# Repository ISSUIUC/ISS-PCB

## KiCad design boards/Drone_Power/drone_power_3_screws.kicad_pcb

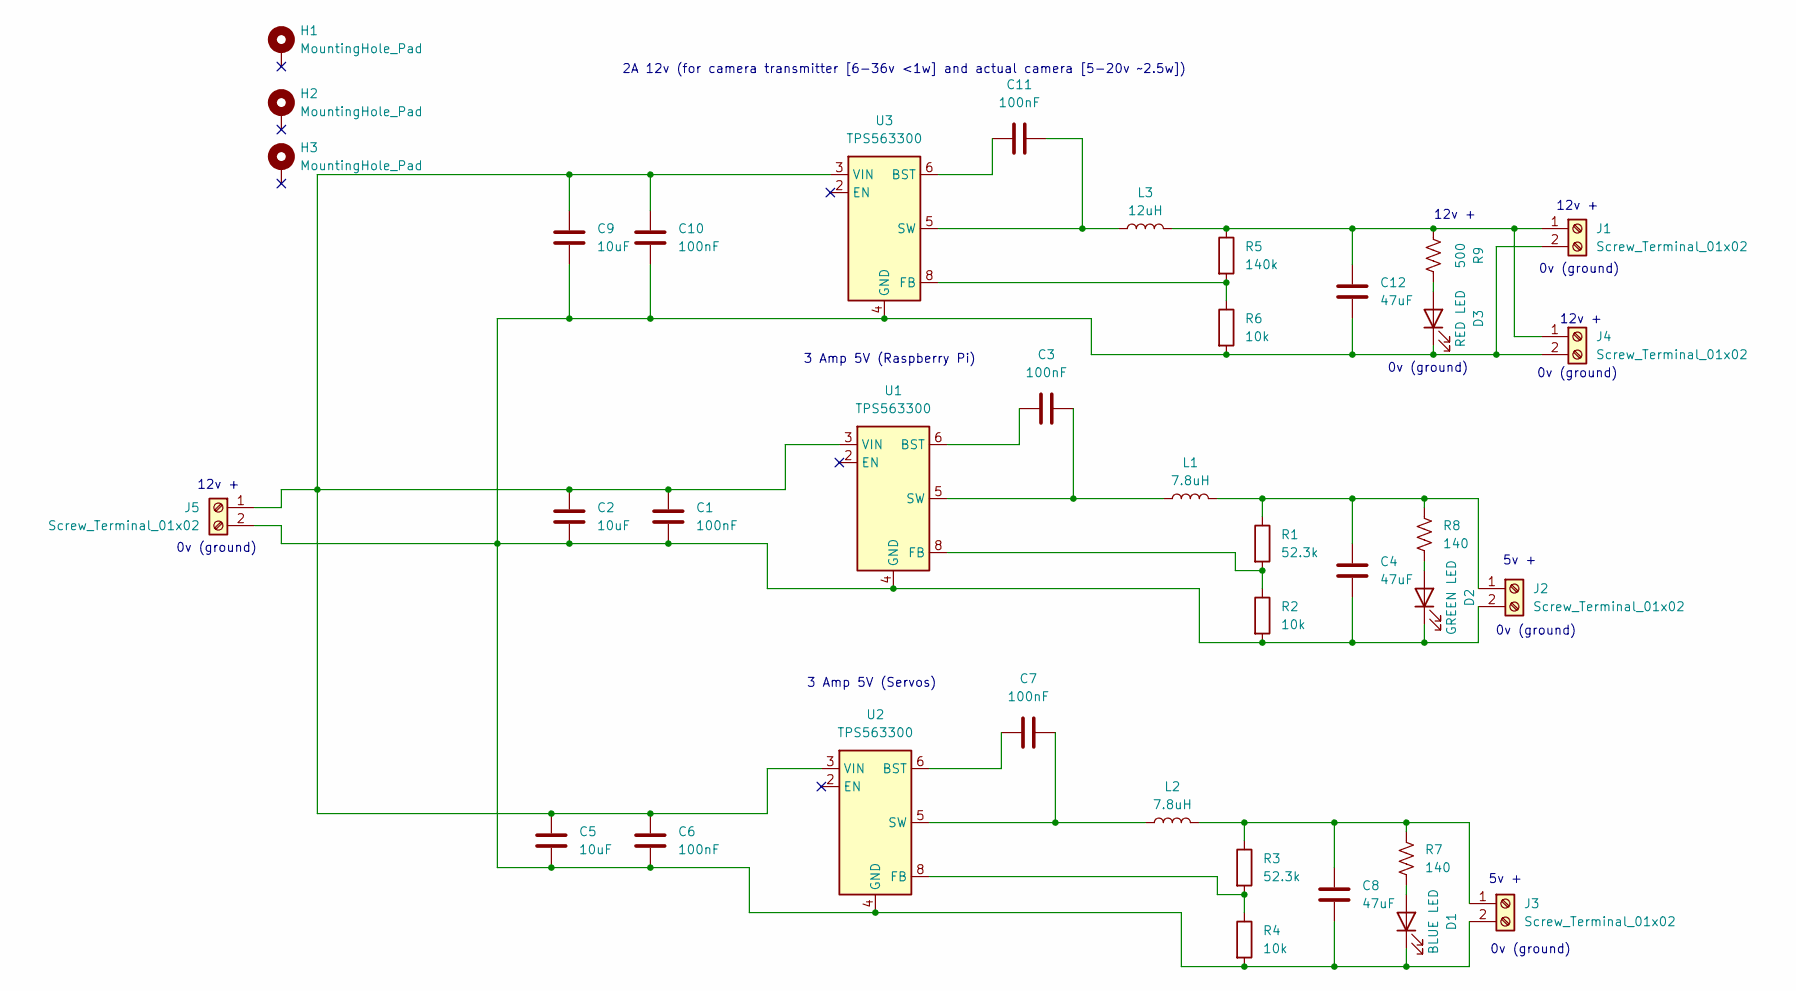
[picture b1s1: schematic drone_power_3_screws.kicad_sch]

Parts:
C1, C3, C6, C7, C10, C11: 100nF; C_0603_1608Metric
C2, C5, C9: 10uF; C_1206_3216Metric
C4, C8, C12: 47uF; C_1210_3225Metric
D1: BLUE LED; LED_0603_1608Metric
D2: GREEN LED; LED_0603_1608Metric
D3: RED LED; LED_0603_1608Metric
H1, H2, H3: MountingHole_Pad; MountingHole_3mm_Pad_Via
J1, J2, J3, J4, J5: Screw_Terminal_01x02; TE_282837-2
L1, L2: 7.8uH; L_Wuerth_HCI-1050
L3: 12uH; IND_XGL6060_COC
R1, R3: 52.3k; R_0603_1608Metric
R2, R4, R6: 10k; R_0603_1608Metric
R5: 140k; R_0603_1608Metric
R7, R8: 140; R_0603_1608Metric
R9: 500; R_0603_1608Metric
U1, U2, U3: TPS563300; SOT-583-8

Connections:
unnamed: D1.2 (A), R7.2
unnamed: C1.2, C2.2, C4.2, C5.2, C6.2, C8.2, C9.2, C10.2, C12.2, D1.1 (K), D2.1 (K), D3.1 (K), J1.2, J2.2, J3.2, J4.2, J5.2, R2.2, R4.2, R6.2, U1.4 (GND), U2.4 (GND), U3.4 (GND)
unnamed: D2.2 (A), R8.2
unnamed: D3.2 (A), R9.2
unnamed: C12.1, J1.1, J4.1, L3.2, R5.1, R9.1
unnamed: C4.1, J2.1, L1.2, R1.1, R8.1
unnamed: C8.1, J3.1, L2.2, R3.1, R7.1
unnamed: C1.1, C2.1, C5.1, C6.1, C9.1, C10.1, J5.1, U1.3 (VIN), U2.3 (VIN), U3.3 (VIN)
unnamed: C3.1, U1.6 (BST)
unnamed: R1.2, R2.1, U1.8 (FB)
unnamed: C3.2, L1.1, U1.5 (SW)
unnamed: C7.1, U2.6 (BST)
unnamed: R3.2, R4.1, U2.8 (FB)
unnamed: C7.2, L2.1, U2.5 (SW)
unnamed: C11.1, U3.6 (BST)
unnamed: R5.2, R6.1, U3.8 (FB)
unnamed: C11.2, L3.1, U3.5 (SW)

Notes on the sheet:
0v (ground)
12v +
3 Amp 5V (Raspberry Pi)
5v +
3 Amp 5V (Servos)
2A 12v (for camera transmitter [6-36v <1w] and actual camera [5-20v ~2.5w])

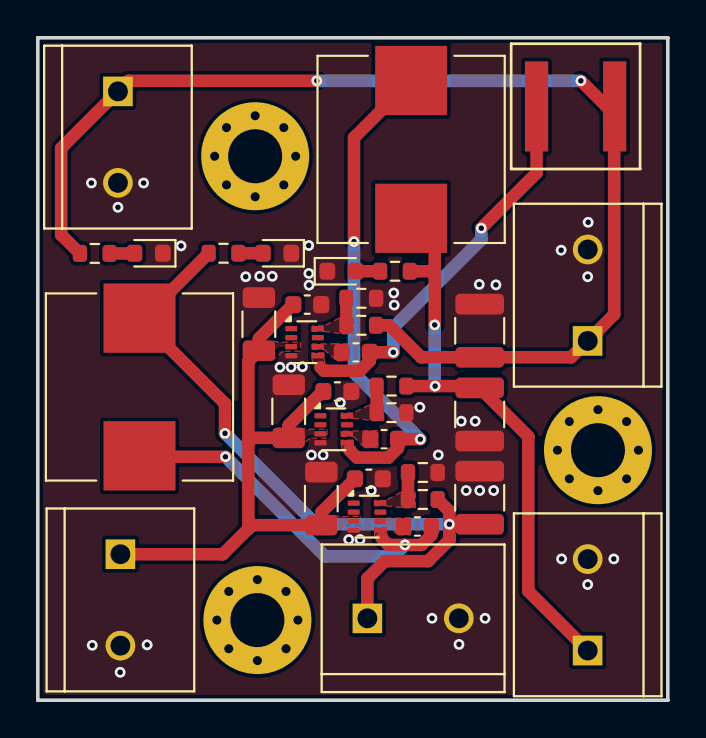
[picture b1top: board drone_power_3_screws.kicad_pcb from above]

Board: 2 copper layers, 35.0 x 36.8 mm, 38 parts (0 on the bottom side), 17 nets.

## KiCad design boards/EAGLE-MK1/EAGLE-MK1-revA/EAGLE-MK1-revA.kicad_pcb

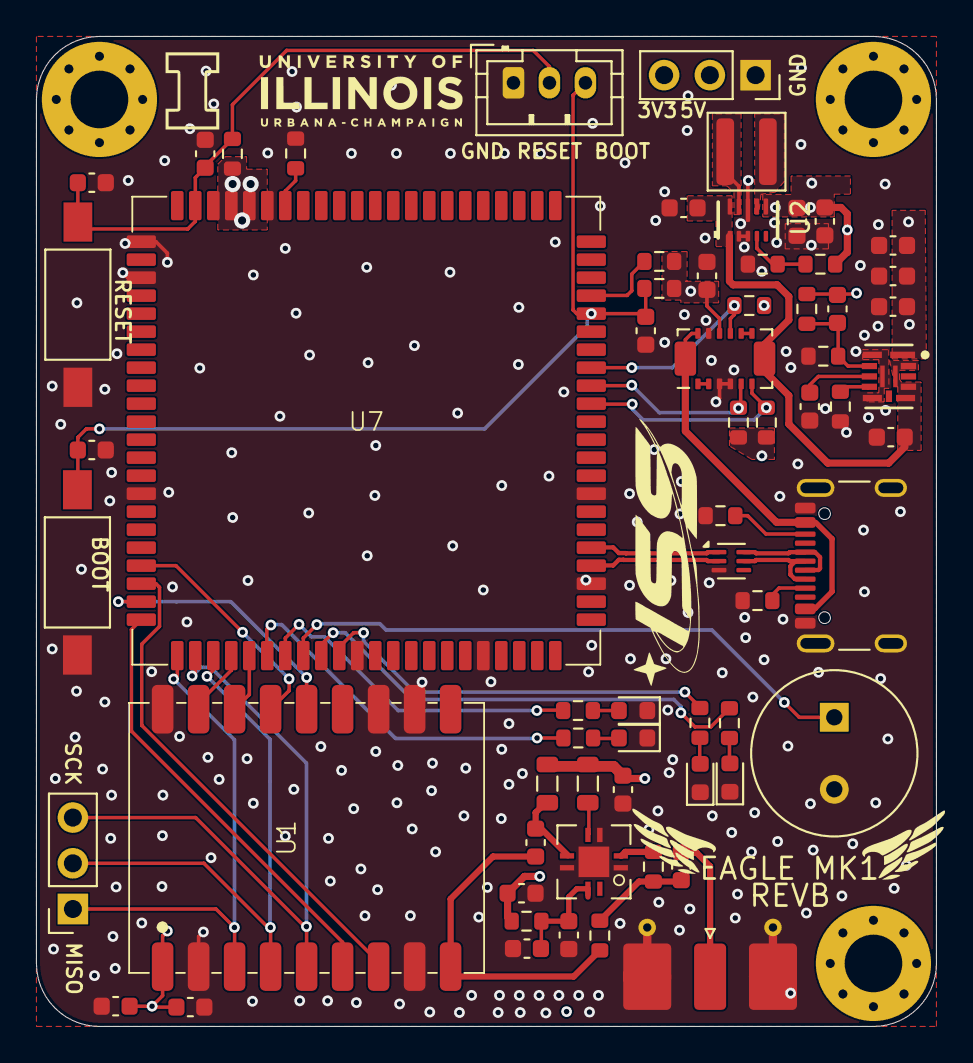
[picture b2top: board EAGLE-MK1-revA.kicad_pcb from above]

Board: 4 copper layers, 50.0 x 55.0 mm, 68 parts (0 on the bottom side), 51 nets.

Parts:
BZ101: Buzzer; MagneticBuzzer_PUI_AT-0927-TT-6-R
C1, C2, C4, C5, C6, C45, C48: 22uF; C_0603_1608Metric
C3, C7, C8, C31, C114: 100nF; C_0603_1608Metric
C10, C34, C36, C120: 1uF; C_0603_1608Metric
C33, C35, C37, C49: 100pF; C_0603_1608Metric
C46: 4.7nF; C_0603_1608Metric
C47: 10pF; C_0603_1608Metric
D104: RED LED; LED_0603_1608Metric
D105: ORANGE LED; LED_0603_1608Metric
D106: GREEN LED; LED_0603_1608Metric
D107: BLUE LED; LED_0603_1608Metric
H101, H103, H104: MountingHole; MountingHole_3.2mm_M3_Pad_Via
J1: SMA; SMA_Molex_73251-2120_EdgeMount_Horizontal
J101: USB4105-GF-A; USB_C_Receptacle_GCT_USB4105-xx-A_16P_TopMnt_Horizontal
J107: Conn_01x03; JST_PH_B3B-PH-K_1x03_P2.00mm_Vertical
J108, J109: Conn_01x03; PinSocket_1x03_P2.54mm_Vertical
L1: 36nH; L_0805_2012Metric
L2: 47nH; L_0805_2012Metric
L4: 470nH; L_Wuerth_MAPI-4030
R1: 806k; R_0603_1608Metric
R2: 91k; R_0603_1608Metric
R3, R4, R118, R119: 0; R_0603_1608Metric
R5, R14, R19, R116: 10k; R_0603_1608Metric
R16: 100k; R_0603_1608Metric
R18: 453k; R_0603_1608Metric
R105, R106: 5.1k; R_0603_1608Metric
R117, R122: 4.7k; R_0603_1608Metric
R140: 20k; R_0603_1608Metric
R141, R142, R143, R144: 470; R_0603_1608Metric
SW2, SW3: SW_Push; SW_SPST_FSMSM
U1: LR2021
U2: TPS63802; VSON-HR-DLA0010A
U4: PMA-545G1+; QFN-8-1EP_3x3mm_P1.2mm_EP1.7x1.7mm
U5: TPSM82813; QFN-FCMOD-VCA0013A
U7: ESP32-P4; ESP32-P4-Module
U101: ECMF02-2AMX6; ST_UQFN-6L_1.5x1.7mm_P0.5mm
U106: INA745x; VQFN-REL0014B

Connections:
+3V3: C4.2, C5.2, C10.1, C31.1, C47.2, C48.2, C114.1, J108.3, R5.2, R18.2, R19.2, R116.1, R117.1, R122.1, R140.2, U1.1 (VCC), U5.1 (VOUT), U7.84 (ESP_VBAT), U7.85 (ESP_3V3), U7.86 (ESP_3V3), U106.11 (VS)
+5V: C2.2, C6.2, C35.2, C36.2, J108.2, L1.2, L2.2, R1.1, R4.2, U2.6 (VOUT)
/Amplifer_Input: R118.1, U4.2 (RFIN)
/Antenna_Connector: C49.2, R118.2, R119.2
/BOOT_SW: C3.1, C8.1, J107.3, R5.1, SW3.1, U7.62 (GPIO35)
/BUZZER: BZ101.1 (-), U7.30 (GPIO21)
/D+: J101.A6 (D+), J101.B6 (D+), U101.6 (D+_out)
/D-: J101.A7 (D-), J101.B7 (D-), U101.5 (D-_out)
/LED_BLUE: R144.1, U7.29 (GPIO20)
/LED_GREEN: R143.1, U7.28 (GPIO13)
/LED_ORANGE: R142.1, U7.31 (GPIO22)
/LED_RED: R141.1, U7.32 (GPIO23)
/LR2021_ANT: C37.1, R119.1, U1.9 (ANT)
/LR2021_BUSY: U1.7 (BUSY), U7.20 (GPIO5)
/LR2021_CS: U1.6 (~CS), U7.22 (GPIO7)
/LR2021_DIO7: U1.17 (DIO7), U7.26 (GPIO11)
/LR2021_DIO8: U1.16 (DIO8), U7.27 (GPIO12)
/LR2021_DIO9: U1.15 (DIO9), U7.19 (GPIO4)
/LR2021_nRST: U1.14 (nRST), U7.21 (GPIO6)
/RESET_SW: C7.1, C120.1, J107.2, R140.1, SW2.1, U7.87 (CHIP_PU)
/SENSE_ALERT: R116.2, U7.59 (GPIO32), U106.10 (ALERT)
/SENSE_SCL: R122.2, U7.57 (GPIO30), U106.6 (SCL)
/SENSE_SDA: R117.2, U7.58 (GPIO31), U106.5 (SDA)
/SPI_MISO: J109.1, U1.3 (MISO), U7.23 (GPIO8)
/SPI_MOSI: J109.2, U1.4 (MOSI), U7.25 (GPIO10)
/SPI_SCK: J109.3, U1.5 (SCK), U7.24 (GPIO9)
/SYS_POWER: J101.A4 (VBUS), J101.A9 (VBUS), J101.B4 (VBUS), J101.B9 (VBUS), U106.13 (VBUS), U106.14 (IS+)
/USB_D+: U7.49 (DP), U101.1 (D+_in)
/USB_D-: U7.48 (DM), U101.2 (D-_in)
/VREG_IN: C1.2, C45.2, U2.1 (EN), U2.10 (VIN), U5.8 (VIN), U5.9 (EN), U5.11 (MODE_SYNC), U5.13 (VIN), U106.7 (IS-)
GND: BZ101.2 (+), C1.1, C2.1, C3.2, C4.1, C5.1, C6.1, C7.2, C8.2, C10.2, C31.2, C33.2, C34.2, C35.1, C36.1, C45.1, C46.1, C48.1, C114.2, C120.2, D104.1 (K), D105.1 (K), D106.1 (K), D107.1 (K), J1.2 (Ext), J101.A1 (GND), J101.A12 (GND), J101.B1 (GND), J101.B12 (GND), J101.S1 (SHIELD), J107.1, J108.1, R2.2, R3.2, R14.2, R16.1, R105.1, R106.1, SW2.2, SW3.2, U1.2 (GND), U1.8 (GND), U1.11 (GND), U1.12 (GND), U1.18 (GND), U2.2 (MODE), U2.3 (AGND), U2.8 (GND), U4.1 (NC), U4.3 (NC), U4.6 (NC), U4.9 (GND), U5.2 (GND), U5.6 (GND), U5.12 (GND), U7.1 (GND), U7.3 (GND), U7.15 (GND), U7.33 (GND), U7.40 (GND), U7.47 (GND), U7.52 (GND), U7.83 (GND), U101.3 (GND), U106.3 (A1), U106.4 (A0), U106.12 (GND)
unnamed: C33.1, C34.1, R4.1, U4.7 (BIAS)
unnamed: D104.2 (A), R141.2
unnamed: D105.2 (A), R142.2
unnamed: D106.2 (A), R143.2
unnamed: D107.2 (A), R144.2
unnamed: C49.1, J1.1 (In)
unnamed: J101.A5 (CC1), R105.2
unnamed: J101.B5 (CC2), R106.2
unnamed: L1.1, U4.4 (BIAS)
unnamed: R1.2, R2.1, U2.4 (FB)
unnamed: L4.1, U2.9 (L1)
unnamed: L4.2, U2.7 (L2)
unnamed: C37.2, L2.1, U4.5 (RFOUT)
unnamed: R14.1, U5.5 (COMP_FSET)
unnamed: C47.1, R16.2, R18.1, U5.3 (FB)
unnamed: C46.2, U5.4 (SS_TR)
unnamed: R19.1, U7.63 (GPIO36)
unnamed: R3.1, U7.82 (GPIO54)
unnamed: U106.1 (SH+), U106.2 (IN+)
unnamed: U106.8 (SH-), U106.9 (IN-)

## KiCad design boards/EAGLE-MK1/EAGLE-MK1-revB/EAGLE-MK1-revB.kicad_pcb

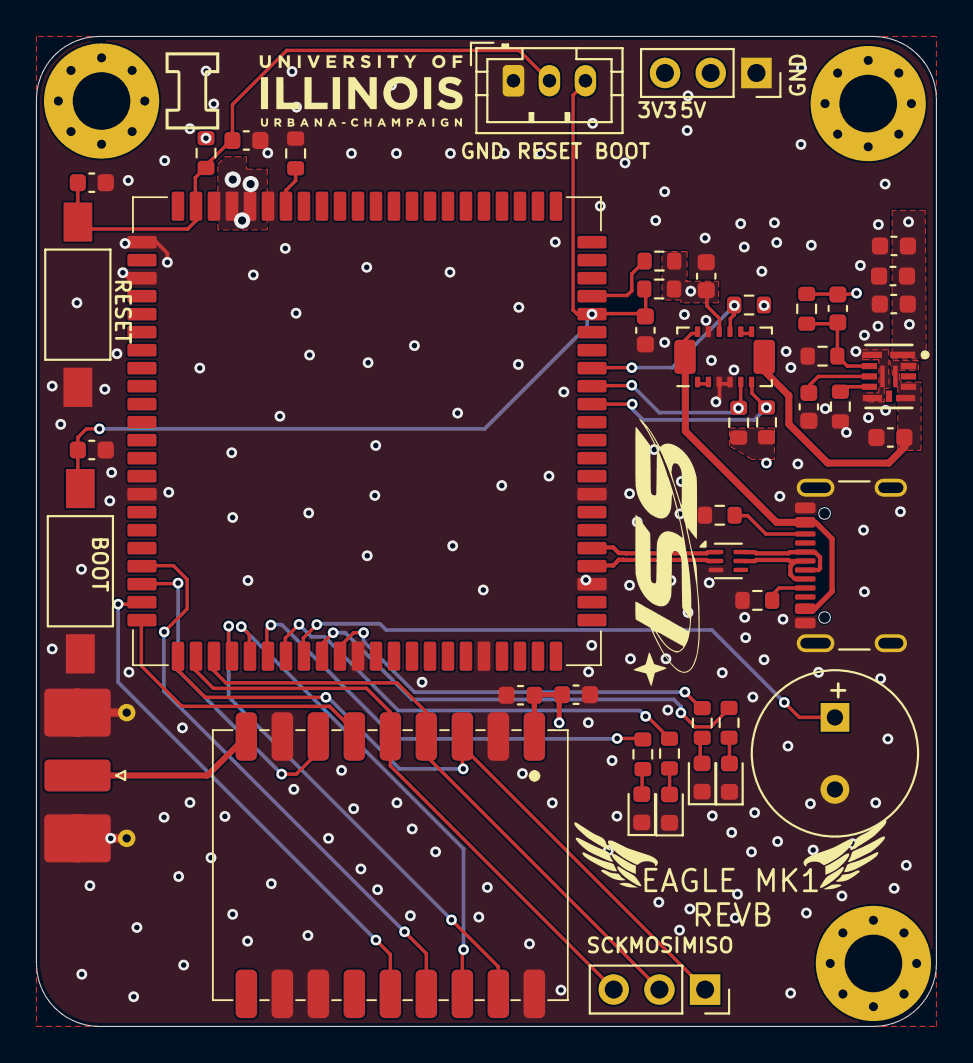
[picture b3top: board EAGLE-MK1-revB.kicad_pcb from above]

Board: 4 copper layers, 50.0 x 55.0 mm, 49 parts (0 on the bottom side), 41 nets.

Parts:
BZ1: Buzzer; MagneticBuzzer_PUI_AT-0927-TT-6-R
C1, C2, C3, C11, C13: 100nF; C_0603_1608Metric
C4, C8, C9, C10: 22uF; C_0603_1608Metric
C5, C12: 1uF; C_0603_1608Metric
C6: 4.7nF; C_0603_1608Metric
C7: 10pF; C_0603_1608Metric
D1: RED LED; LED_0603_1608Metric
D2: ORANGE LED; LED_0603_1608Metric
D3: GREEN LED; LED_0603_1608Metric
D4: BLUE LED; LED_0603_1608Metric
H1, H2, H3: MountingHole; MountingHole_3.2mm_M3_Pad_Via
J1: USB4105-GF-A; USB_C_Receptacle_GCT_USB4105-xx-A_16P_TopMnt_Horizontal
J2, J5: Conn_01x03; PinSocket_1x03_P2.54mm_Vertical
J3: Conn_01x03; JST_PH_B3B-PH-K_1x03_P2.00mm_Vertical
J4: SMA; SMA_Molex_73251-2120_EdgeMount_Horizontal
R1, R2: 5.1k; R_0603_1608Metric
R3: 0; R_0603_1608Metric
R4, R5: 4.7k; R_0603_1608Metric
R6, R7, R9, R16: 10k; R_0603_1608Metric
R8: 20k; R_0603_1608Metric
R10, R11, R12, R13: 470; R_0603_1608Metric
R14: 453k; R_0603_1608Metric
R15: 100k; R_0603_1608Metric
SW1, SW2: SW_Push; SW_SPST_FSMSM
U1: ECMF02-2AMX6; ST_UQFN-6L_1.5x1.7mm_P0.5mm
U2: ESP32-P4; ESP32-P4-Module
U3: TPSM82813; QFN-FCMOD-VCA0013A
U4: INA745x; VQFN-REL0014B
U5: LR2021

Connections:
+3V3: C7.2, C8.2, C9.2, C10.2, C11.1, C12.1, C13.1, J2.3, R4.1, R5.1, R6.2, R7.2, R8.2, R14.2, R16.1, U2.84 (ESP_VBAT), U2.85 (ESP_3V3), U2.86 (ESP_3V3), U3.1 (VOUT), U4.11 (VS), U5.1 (VCC)
/BOOT_SW: C2.1, C3.1, J3.3, R7.1, SW2.1, U2.62 (GPIO35)
/BUZZER: BZ1.1 (-), U2.30 (GPIO21)
/D+: J1.A6 (D+), J1.B6 (D+), U1.6 (D+_out)
/D-: J1.A7 (D-), J1.B7 (D-), U1.5 (D-_out)
/LED_BLUE: R13.1, U2.29 (GPIO20)
/LED_GREEN: R12.1, U2.28 (GPIO13)
/LED_ORANGE: R11.1, U2.31 (GPIO22)
/LED_RED: R10.1, U2.32 (GPIO23)
/LR2021_ANT: J4.1 (In), U5.9 (ANT)
/LR2021_BUSY: U2.20 (GPIO5), U5.7 (BUSY)
/LR2021_CS: U2.22 (GPIO7), U5.6 (~CS)
/LR2021_DIO7: U2.26 (GPIO11), U5.17 (DIO7)
/LR2021_DIO8: U2.27 (GPIO12), U5.16 (DIO8)
/LR2021_DIO9: U2.19 (GPIO4), U5.15 (DIO9)
/LR2021_nRST: U2.21 (GPIO6), U5.14 (nRST)
/RESET_SW: C1.1, C5.1, J3.2, R8.1, SW1.1, U2.87 (CHIP_PU)
/SENSE_ALERT: R16.2, U2.59 (GPIO32), U4.10 (ALERT)
/SENSE_SCL: R5.2, U2.57 (GPIO30), U4.6 (SCL)
/SENSE_SDA: R4.2, U2.58 (GPIO31), U4.5 (SDA)
/SPI_MISO: J5.1, U2.23 (GPIO8), U5.3 (MISO)
/SPI_MOSI: J5.2, U2.25 (GPIO10), U5.4 (MOSI)
/SPI_SCK: J5.3, U2.24 (GPIO9), U5.5 (SCK)
/SYS_POWER: J1.A4 (VBUS), J1.A9 (VBUS), J1.B4 (VBUS), J1.B9 (VBUS), U4.13 (VBUS), U4.14 (IS+)
/USB_D+: U1.1 (D+_in), U2.49 (DP)
/USB_D-: U1.2 (D-_in), U2.48 (DM)
/VREG_IN: C4.2, U3.8 (VIN), U3.9 (EN), U3.11 (MODE_SYNC), U3.13 (VIN), U4.7 (IS-)
GND: BZ1.2 (+), C1.2, C2.2, C3.2, C4.1, C5.2, C6.1, C8.1, C9.1, C10.1, C11.2, C12.2, C13.2, D1.1 (K), D2.1 (K), D3.1 (K), D4.1 (K), J1.A1 (GND), J1.A12 (GND), J1.B1 (GND), J1.B12 (GND), J1.S1 (SHIELD), J2.1, J3.1, J4.2 (Ext), R1.1, R2.1, R3.2, R9.2, R15.1, SW1.2, SW2.2, U1.3 (GND), U2.1 (GND), U2.3 (GND), U2.15 (GND), U2.33 (GND), U2.40 (GND), U2.47 (GND), U2.52 (GND), U2.83 (GND), U3.2 (GND), U3.6 (GND), U3.12 (GND), U4.3 (A1), U4.4 (A0), U4.12 (GND), U5.2 (GND), U5.8 (GND), U5.11 (GND), U5.12 (GND), U5.18 (GND)
unnamed: D1.2 (A), R10.2
unnamed: D2.2 (A), R11.2
unnamed: D3.2 (A), R12.2
unnamed: D4.2 (A), R13.2
unnamed: J1.A5 (CC1), R1.2
unnamed: J1.B5 (CC2), R2.2
unnamed: R6.1, U2.63 (GPIO36)
unnamed: R3.1, U2.82 (GPIO54)
unnamed: R9.1, U3.5 (COMP_FSET)
unnamed: C7.1, R14.1, R15.2, U3.3 (FB)
unnamed: C6.2, U3.4 (SS_TR)
unnamed: U4.1 (SH+), U4.2 (IN+)
unnamed: U4.8 (SH-), U4.9 (IN-)

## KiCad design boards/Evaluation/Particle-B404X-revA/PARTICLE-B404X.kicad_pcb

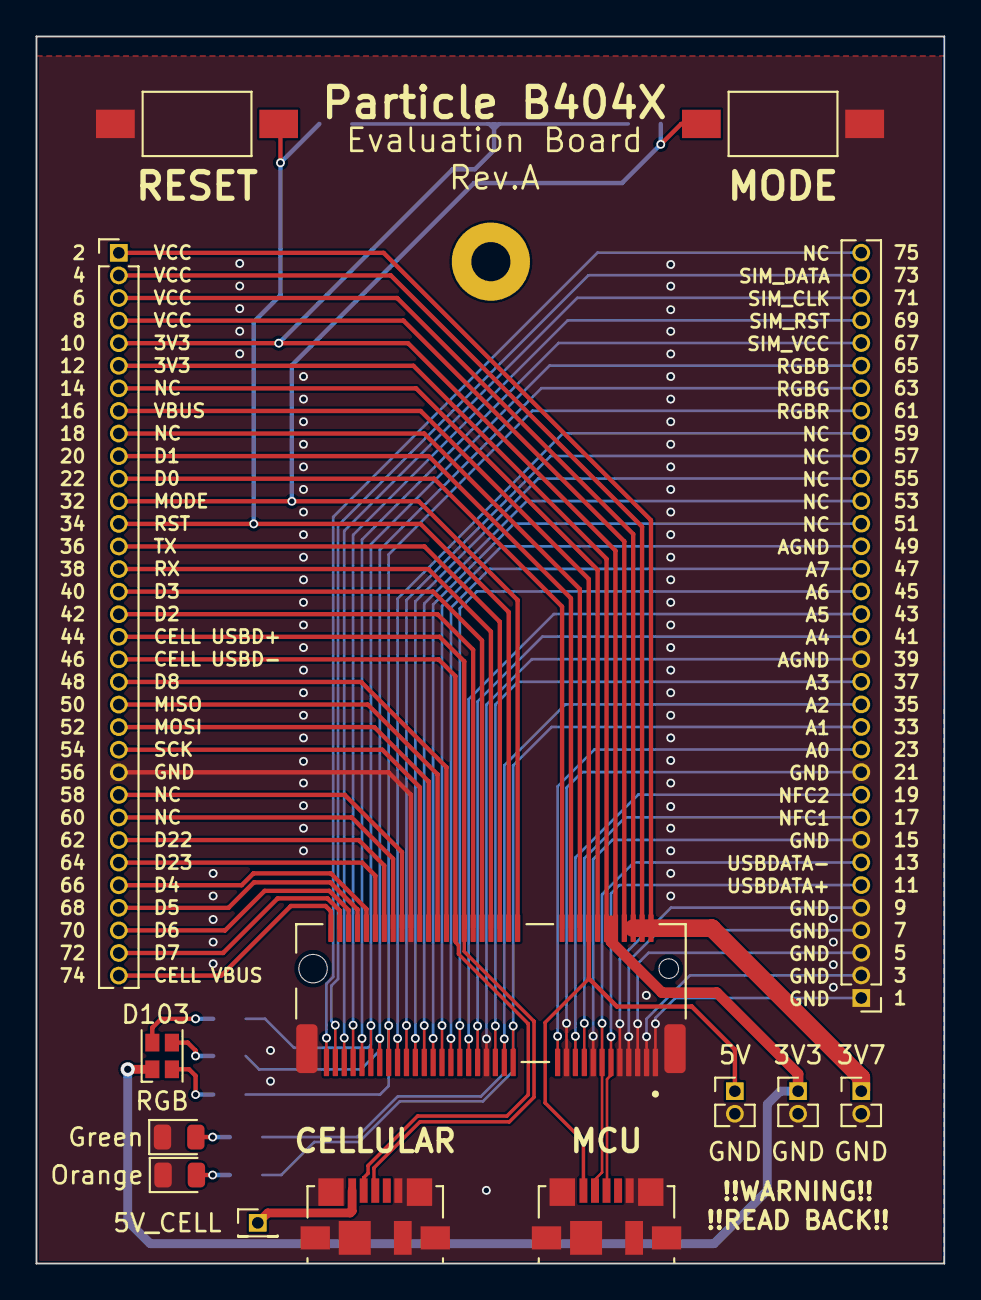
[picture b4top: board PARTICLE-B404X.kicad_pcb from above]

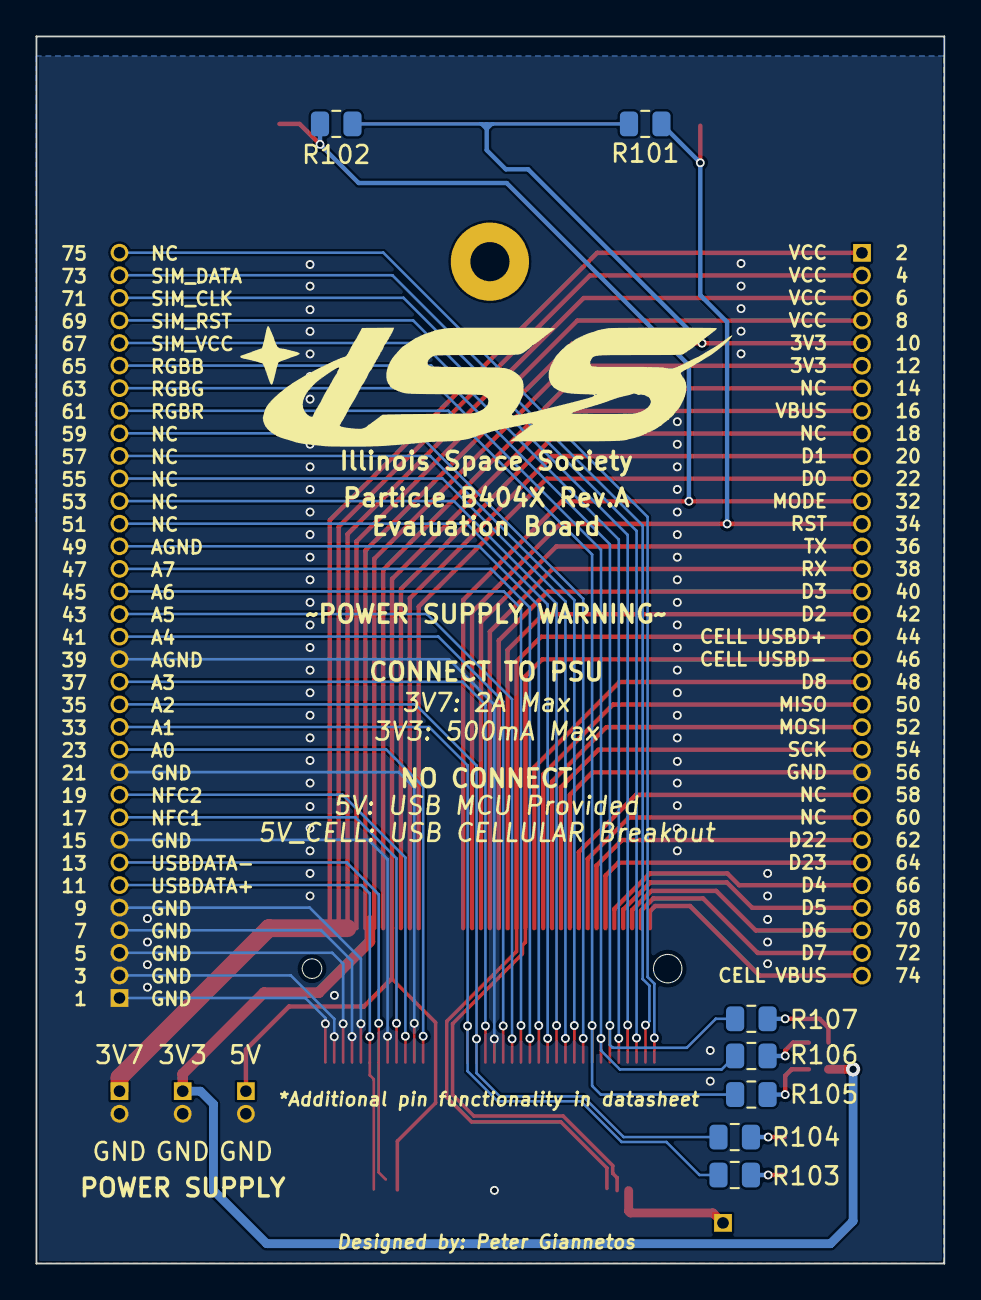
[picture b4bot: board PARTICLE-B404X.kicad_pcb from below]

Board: 2 copper layers, 51.1 x 69.0 mm, 22 parts (7 on the bottom side), 61 nets.

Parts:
D101: ORANGE LED; LED_0805_2012Metric
D102: GREEN LED; LED_0805_2012Metric
D103: LED_ABGR; LED_Cree-PLCC4_2x2mm_CW
H101: MountingHole; MountingHole_2.2mm_M2_Pad
J101: B404X; TE_21992304
J102: Conn_01x34; PinHeader_1x34_P1.27mm_Vertical
J103: Conn_01x33; PinHeader_1x33_P1.27mm_Vertical
J104, J108: USB_B_Micro; USB_Micro-B_Molex_47346-0001
J105, J106, J107: Conn_01x02; PinHeader_1x02_P1.27mm_Vertical
J109: Conn_01x01; PinHeader_1x01_P1.27mm_Vertical
R101, R102: 10K; R_0805_2012Metric
R103, R104: 470; R_0805_2012Metric
R105, R106, R107: 1K; R_0805_2012Metric
SW101, SW102: SW_Push; SW_SPST_FSMSM

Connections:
/5V_CELL: J108.1 (VBUS), J109.1
/B404X_2: J101.2, J101.4, J101.6, J101.8, J103.1, J103.2, J103.3, J103.4, J106.1
/B404X_10: D103.1 (A), J101.10, J101.12, J103.5, J103.6, J107.1, R101.1, R102.1
/B404X_11: J101.11, J102.6, J104.3 (D+)
/B404X_13: J101.13, J102.7, J104.2 (D-)
/B404X_14: J101.14, J103.7
/B404X_16: J101.16, J103.8, J104.1 (VBUS), J105.1
/B404X_17: J101.17, J102.9
/B404X_18: J101.18, J103.9
/B404X_19: J101.19, J102.10
/B404X_20: J101.20, J103.10
/B404X_22: J101.22, J103.11
/B404X_23: J101.23, J102.12
/B404X_32: J101.32, J103.12, R102.2, SW102.2
/B404X_33: J101.33, J102.13, R103.1
/B404X_34: J101.34, J103.13, R101.2, SW101.2
/B404X_35: J101.35, J102.14, R104.1
/B404X_36: J101.36, J103.14
/B404X_37: J101.37, J102.15
/B404X_38: J101.38, J103.15
/B404X_40: J101.40, J103.16
/B404X_41: J101.41, J102.17
/B404X_42: J101.42, J103.17
/B404X_43: J101.43, J102.18
/B404X_44: J101.44, J103.18, J108.3 (D+)
/B404X_45: J101.45, J102.19
/B404X_46: J101.46, J103.19, J108.2 (D-)
/B404X_47: J101.47, J102.20
/B404X_48: J101.48, J103.20
/B404X_49: J101.49, J102.21
/B404X_50: J101.50, J103.21
/B404X_51: J101.51, J102.22
/B404X_52: J101.52, J103.22
/B404X_53: J101.53, J102.23
/B404X_54: J101.54, J103.23
/B404X_55: J101.55, J102.24
/B404X_57: J101.57, J102.25
/B404X_58: J101.58, J103.25
/B404X_59: J101.59, J102.26
/B404X_60: J101.60, J103.26
/B404X_61: J101.61, J102.27, R105.1
/B404X_62: J101.62, J103.27
/B404X_63: J101.63, J102.28, R106.1
/B404X_64: J101.64, J103.28
/B404X_65: J101.65, J102.29, R107.1
/B404X_66: J101.66, J103.29
/B404X_67: J101.67, J102.30
/B404X_68: J101.68, J103.30
/B404X_69: J101.69, J102.31
/B404X_70: J101.70, J103.31
/B404X_71: J101.71, J102.32
/B404X_72: J101.72, J103.32
/B404X_73: J101.73, J102.33
/B404X_74: J101.74, J103.33
/B404X_75: J101.75, J102.34
GND: D101.1 (K), D102.1 (K), J101.1, J101.3, J101.5, J101.7, J101.9, J101.15, J101.21, J101.39, J101.56, J101.S1 (SHIELD), J102.1, J102.2, J102.3, J102.4, J102.5, J102.8, J102.11, J102.16, J103.24, J104.5 (GND), J104.6 (Shield), J105.2, J106.2, J107.2, J108.5 (GND), J108.6 (Shield), SW101.1, SW102.1
unnamed: D101.2 (A), R103.2
unnamed: D102.2 (A), R104.2
unnamed: D103.2 (BK), R107.2
unnamed: D103.3 (GK), R106.2
unnamed: D103.4 (RK), R105.2

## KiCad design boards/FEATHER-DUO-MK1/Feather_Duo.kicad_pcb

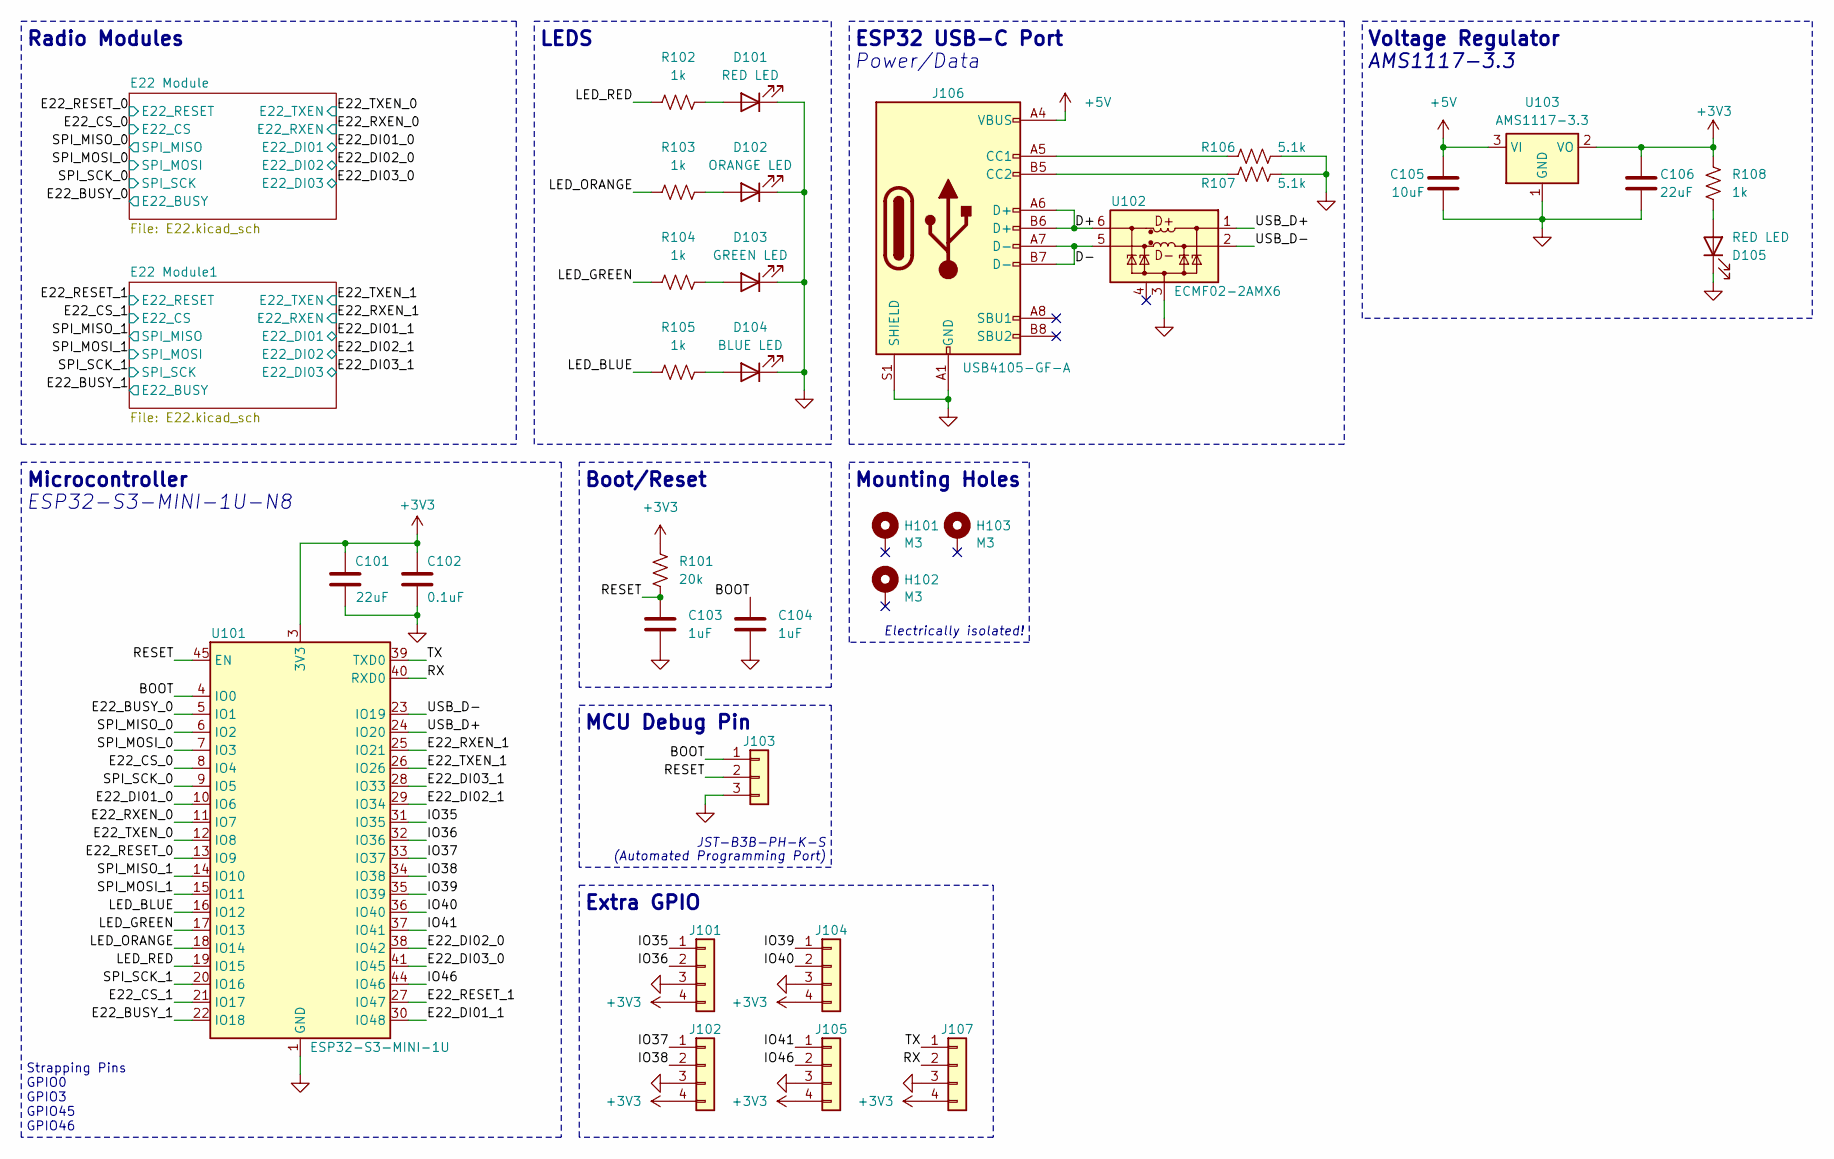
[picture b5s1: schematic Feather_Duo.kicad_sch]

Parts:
C101, C106: 22uF; C_0603_1608Metric
C102: 0.1uF; C_0603_1608Metric
C103, C104: 1uF; C_0603_1608Metric
C105: 10uF; C_0603_1608Metric
D101, D105: RED LED; LED_0603_1608Metric
D102: ORANGE LED; LED_0603_1608Metric
D103: GREEN LED; LED_0603_1608Metric
D104: BLUE LED; LED_0603_1608Metric
H101, H102, H103: M3; MountingHole_3.2mm_M3_Pad_Via
J101, J102, J104, J105, J107: Conn_01x04; PinHeader_1x04_P2.54mm_Vertical
J103: Conn_01x03; JST_PH_B3B-PH-K_1x03_P2.00mm_Vertical
J106: USB4105-GF-A; USB_C_Receptacle_GCT_USB4105-xx-A_16P_TopMnt_Horizontal
R101: 20k; R_0603_1608Metric
R102, R103, R104, R105, R108: 1k; R_0603_1608Metric
R106, R107: 5.1k; R_0603_1608Metric
U101: ESP32-S3-MINI-1U; ESP32-S2-MINI-1U
U102: ECMF02-2AMX6; ST_UQFN-6L_1.5x1.7mm_P0.5mm
U103: AMS1117-3.3; SOT-223-3_TabPin2

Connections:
+3V3: C101.2, C102.2, C106.1, J101.4, J102.4, J104.4, J105.4, J107.4, R101.1, R108.1, U101.3 (3V3), U103.2 (VO); also elsewhere on the board
+5V: C105.1, J106.A4 (VBUS), J106.A9 (VBUS), J106.B4 (VBUS), J106.B9 (VBUS), U103.3 (VI)
/BOOT: C104.1, J103.1, U101.4 (IO0)
/D+: J106.A6 (D+), J106.B6 (D+), U102.6 (D+_out)
/D-: J106.A7 (D-), J106.B7 (D-), U102.5 (D-_out)
/E22_BUSY_0: U101.5 (IO1); also elsewhere on the board
/E22_BUSY_1: U101.22 (IO18); also elsewhere on the board
/E22_CS_0: U101.8 (IO4); also elsewhere on the board
/E22_CS_1: U101.21 (IO17); also elsewhere on the board
/E22_DI01_0: U101.10 (IO6); also elsewhere on the board
/E22_DI01_1: U101.30 (IO48); also elsewhere on the board
/E22_DI02_0: U101.38 (IO42); also elsewhere on the board
/E22_DI02_1: U101.29 (IO34); also elsewhere on the board
/E22_DI03_0: U101.41 (IO45); also elsewhere on the board
/E22_DI03_1: U101.28 (IO33); also elsewhere on the board
/E22_RESET_0: U101.13 (IO9); also elsewhere on the board
/E22_RESET_1: U101.27 (IO47); also elsewhere on the board
/E22_RXEN_0: U101.11 (IO7); also elsewhere on the board
/E22_RXEN_1: U101.25 (IO21); also elsewhere on the board
/E22_TXEN_0: U101.12 (IO8); also elsewhere on the board
/E22_TXEN_1: U101.26 (IO26); also elsewhere on the board
/IO35: J101.1, U101.31 (IO35)
/IO36: J101.2, U101.32 (IO36)
/IO37: J102.1, U101.33 (IO37)
/IO38: J102.2, U101.34 (IO38)
/IO39: J104.1, U101.35 (IO39)
/IO40: J104.2, U101.36 (IO40)
/IO41: J105.1, U101.37 (IO41)
/IO46: J105.2, U101.44 (IO46)
/LED_BLUE: R105.1, U101.16 (IO12)
/LED_GREEN: R104.1, U101.17 (IO13)
/LED_ORANGE: R103.1, U101.18 (IO14)
/LED_RED: R102.1, U101.19 (IO15)
/RESET: C103.1, J103.2, R101.2, U101.45 (EN)
/RX: J107.2, U101.40 (RXD0)
/SPI_MISO_0: U101.6 (IO2); also elsewhere on the board
/SPI_MISO_1: U101.14 (IO10); also elsewhere on the board
/SPI_MOSI_0: U101.7 (IO3); also elsewhere on the board
/SPI_MOSI_1: U101.15 (IO11); also elsewhere on the board
/SPI_SCK_0: U101.9 (IO5); also elsewhere on the board
/SPI_SCK_1: U101.20 (IO16); also elsewhere on the board
/TX: J107.1, U101.39 (TXD0)
/USB_D+: U101.24 (IO20), U102.1 (D+_in)
/USB_D-: U101.23 (IO19), U102.2 (D-_in)
GND: C101.1, C102.1, C103.2, C104.2, C105.2, C106.2, D101.1 (K), D102.1 (K), D103.1 (K), D104.1 (K), D105.1 (K), J101.3, J102.3, J103.3, J104.3, J105.3, J106.A1 (GND), J106.A12 (GND), J106.B1 (GND), J106.B12 (GND), J106.S1 (SHIELD), J107.3, R106.2, R107.2, U101.1 (GND), U101.2 (GND), U101.42 (GND), U101.43 (GND), U101.46 (GND), U101.47 (GND), U101.48 (GND), U101.49 (GND), U101.50 (GND), U101.51 (GND), U101.52 (GND), U101.53 (GND), U101.54 (GND), U101.55 (GND), U101.56 (GND), U101.57 (GND), U101.58 (GND), U101.59 (GND), U101.60 (GND), U101.61 (GND), U101.62 (GND), U101.63 (GND), U101.64 (GND), U101.65 (GND), U102.3 (GND), U103.1 (GND); also elsewhere on the board
unnamed: D101.2 (A), R102.2
unnamed: D102.2 (A), R103.2
unnamed: D103.2 (A), R104.2
unnamed: D104.2 (A), R105.2
unnamed: D105.2 (A), R108.2
unnamed: J106.A5 (CC1), R106.1
unnamed: J106.B5 (CC2), R107.1

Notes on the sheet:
Microcontroller
MCU Debug Pin
Electrically isolated!
LEDS
Voltage Regulator
AMS1117-3.3
JST-B3B-PH-K-S
Radio Modules
ESP32-S3-MINI-1U-N8
Extra GPIO
ESP32 USB-C Port
Strapping Pins GPIO0 GPIO3 GPIO45 GPIO46
Power/Data
(Automated Programming Port)
Mounting Holes
Boot/Reset

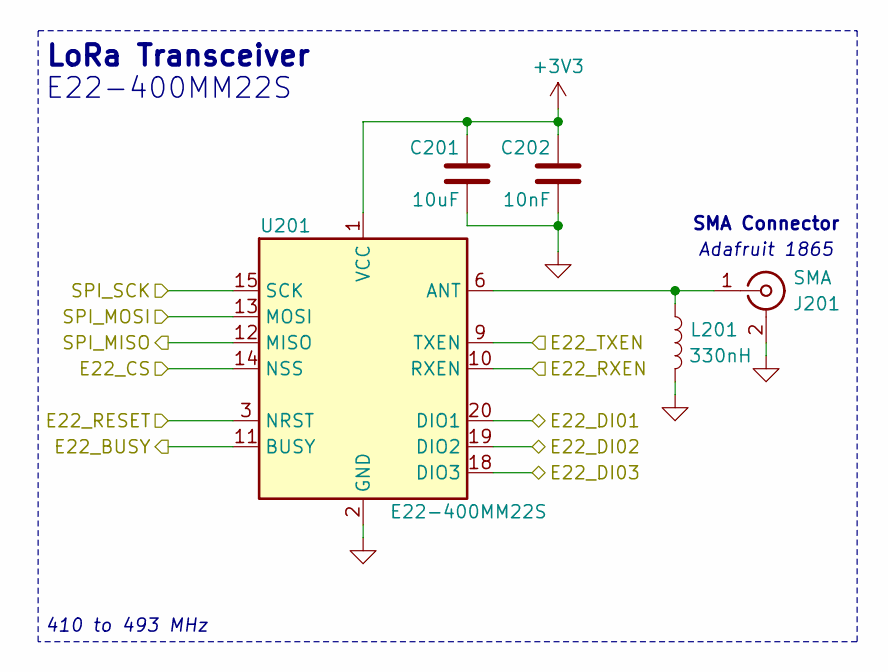
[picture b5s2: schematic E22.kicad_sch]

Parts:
C201: 10uF; C_0603_1608Metric
C202: 10nF; C_0603_1608Metric
J201: SMA; SMA_Molex_73251-2120_EdgeMount_Horizontal
L201: 330nH; L_0603_1608Metric
U201: E22-400MM22S

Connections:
+3V3: C201.1, C202.1, U201.1 (VCC); also elsewhere on the board
/E22_BUSY_0: U201.11 (BUSY); also elsewhere on the board
/E22_CS_0: U201.14 (NSS); also elsewhere on the board
/E22_DI01_0: U201.20 (DIO1); also elsewhere on the board
/E22_DI02_0: U201.19 (DIO2); also elsewhere on the board
/E22_DI03_0: U201.18 (DIO3); also elsewhere on the board
/E22_RESET_0: U201.3 (NRST); also elsewhere on the board
/E22_RXEN_0: U201.10 (RXEN); also elsewhere on the board
/E22_TXEN_0: U201.9 (TXEN); also elsewhere on the board
/SPI_MISO_0: U201.12 (MISO); also elsewhere on the board
/SPI_MOSI_0: U201.13 (MOSI); also elsewhere on the board
/SPI_SCK_0: U201.15 (SCK); also elsewhere on the board
GND: C201.2, C202.2, J201.2 (Ext), L201.2, U201.2 (GND), U201.7 (GND), U201.16 (GND); also elsewhere on the board
unnamed: J201.1 (In), L201.1, U201.6 (ANT)

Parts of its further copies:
C301: 10uF; C_0603_1608Metric
C302: 10nF; C_0603_1608Metric
J301: SMA; SMA_Molex_73251-2120_EdgeMount_Horizontal
L301: 330nH; L_0603_1608Metric
U301: E22-400MM22S

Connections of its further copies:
+3V3: C301.1, C302.1, U301.1 (VCC); also elsewhere on the board
/E22_BUSY_1: U301.11 (BUSY); also elsewhere on the board
/E22_CS_1: U301.14 (NSS); also elsewhere on the board
/E22_DI01_1: U301.20 (DIO1); also elsewhere on the board
/E22_DI02_1: U301.19 (DIO2); also elsewhere on the board
/E22_DI03_1: U301.18 (DIO3); also elsewhere on the board
/E22_RESET_1: U301.3 (NRST); also elsewhere on the board
/E22_RXEN_1: U301.10 (RXEN); also elsewhere on the board
/E22_TXEN_1: U301.9 (TXEN); also elsewhere on the board
/SPI_MISO_1: U301.12 (MISO); also elsewhere on the board
/SPI_MOSI_1: U301.13 (MOSI); also elsewhere on the board
/SPI_SCK_1: U301.15 (SCK); also elsewhere on the board
GND: C301.2, C302.2, J301.2 (Ext), L301.2, U301.2 (GND), U301.7 (GND), U301.16 (GND); also elsewhere on the board
unnamed: J301.1 (In), L301.1, U301.6 (ANT)

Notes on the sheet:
SMA Connector
LoRa Transceiver
E22-400MM22S
410 to 493 MHz
Adafruit 1865

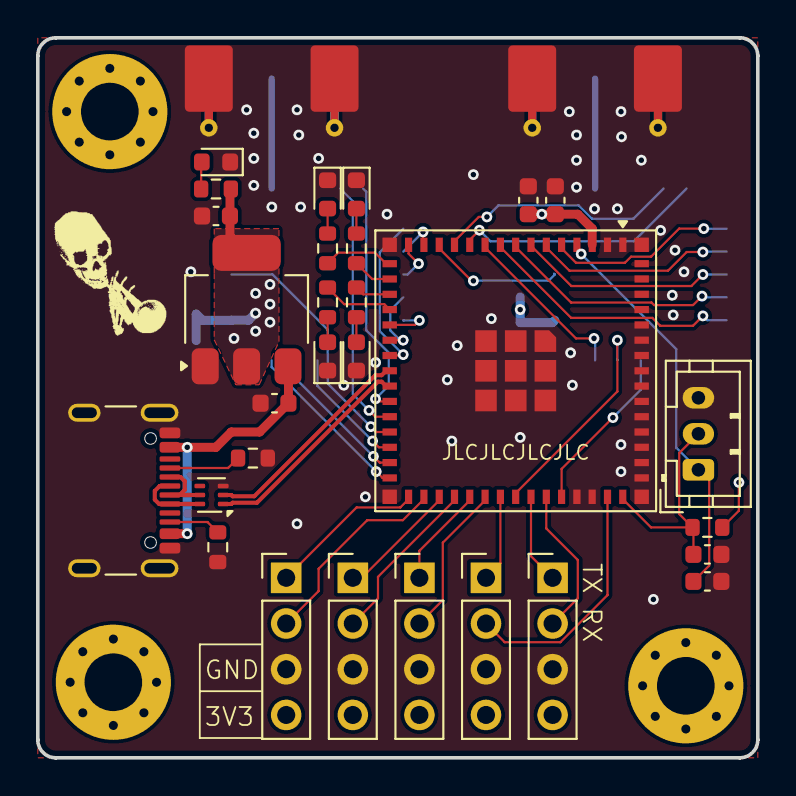
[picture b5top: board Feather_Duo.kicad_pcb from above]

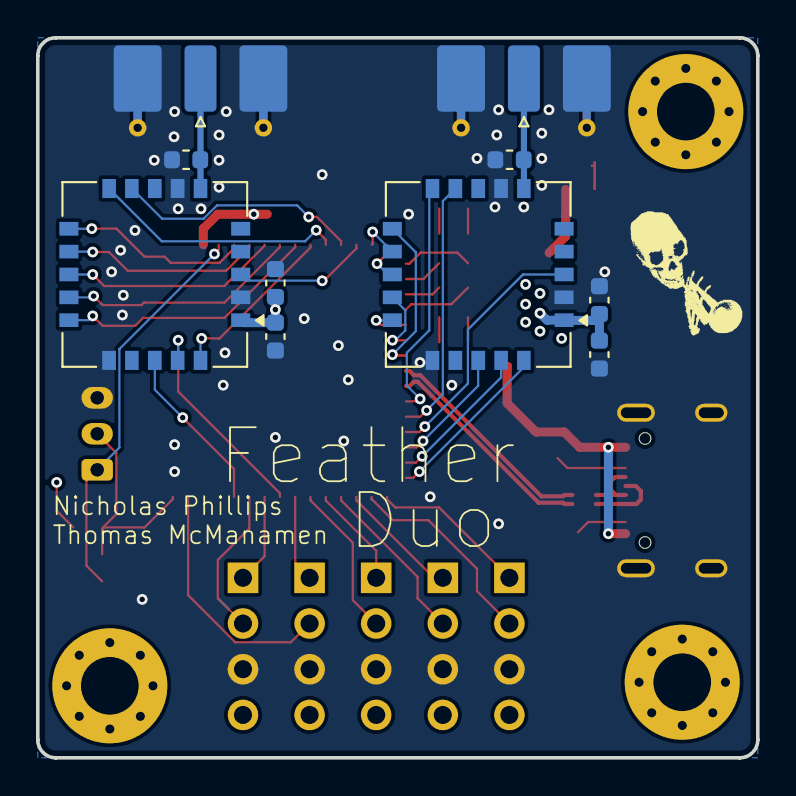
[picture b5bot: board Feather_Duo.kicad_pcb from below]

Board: 4 copper layers, 40.0 x 40.0 mm, 42 parts (10 on the bottom side), 54 nets.
